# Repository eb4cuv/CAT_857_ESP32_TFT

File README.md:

# CAT_857_ESP32_TFT

This software is based on the well-known ESP32 processor and a 3.5-inch (480x320) TFT touch screen. In its design it has been thought mainly in the simplicity of construction and use as well as in reducing costs.

It is designed to work with the FT857. In other models such as FT817 and FT897 it can work but not all functions are available because the memory map is diferent. It is a pending issue to be developed in the future.

------------------------------------------------------
Este proyecto se ha realizado sobre la base del ya conocido procesador ESP32 https://www.espressif.com/en/products/devkits/esp32-devkitc y un TFT tactil de 3,5 pulgadas (480x320) http://www.lcdwiki.com/3.5inch_SPI_Module_ILI9488_SKU:MSP3520. En su diseño se ha pensado principalmente en la sencillez de construccion y uso asi como en abaratar costes.

Esta diseñado para funcionar con la Yaesu FT857. En otros modelos como la FT817 y FT897 puede funcionar tambien pero no todas las funciones estan disponibles porque la memmoria de unas y otras es disitinta. Es un tema pendiente a desarrollar en un futuro.

------------------------------------------------------

## Estas son algunas de las pantallas:

## Pantalla principal con los VFO's

## Radio de OM y OC

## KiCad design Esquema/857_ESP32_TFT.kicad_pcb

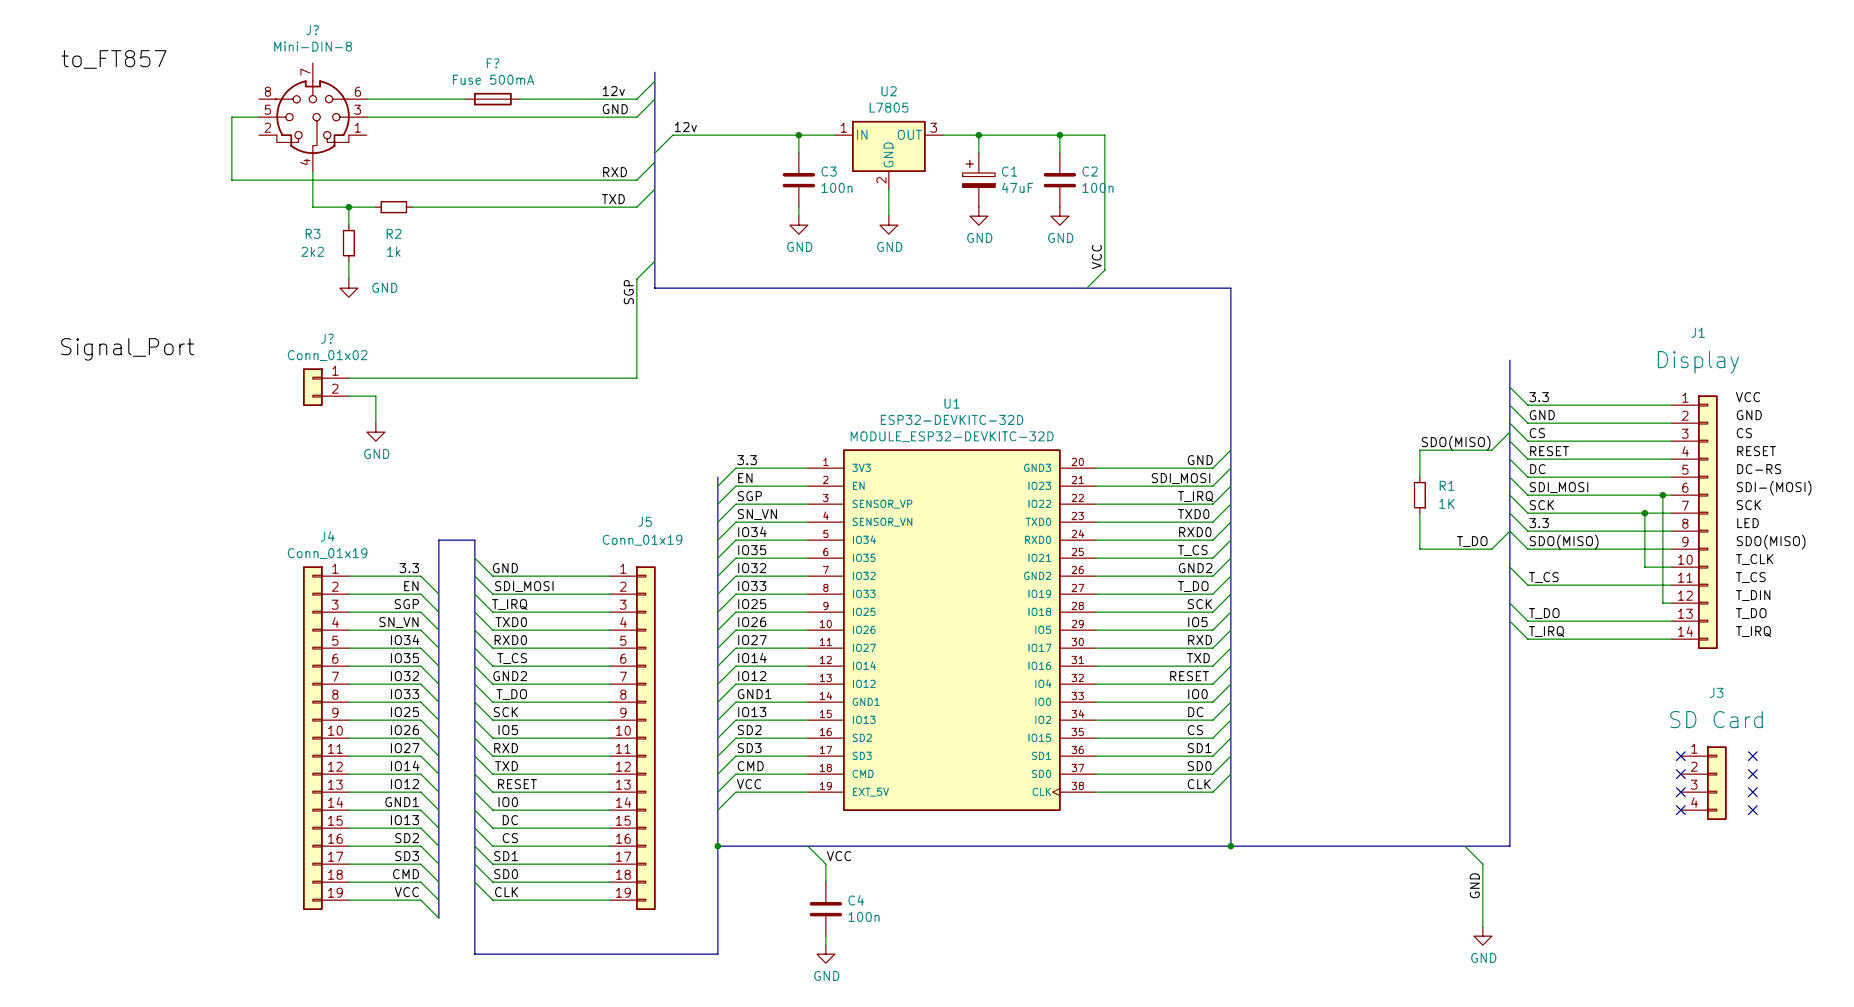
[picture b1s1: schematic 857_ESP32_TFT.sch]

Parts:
C1: 47uF
C2, C3, C4: 100n; C_Rect_L4.6mm_W3.0mm_P2.50mm_MKS02_FKP02
J1: Display; PinHeader_1x14_P2.54mm_Vertical
J3: SD Card; PinHeader_1x04_P2.54mm_Vertical
J4, J5: Conn_01x19; PinHeader_1x19_P2.54mm_Vertical
R1: 1K; R_Axial_DIN0309_L9.0mm_D3.2mm_P12.70mm_Horizontal
R2: 1k; R_Axial_DIN0309_L9.0mm_D3.2mm_P12.70mm_Horizontal
R3: 2k2; R_Axial_DIN0309_L9.0mm_D3.2mm_P12.70mm_Horizontal
U1: ESP32-DEVKITC-32D; MODULE_ESP32-DEVKITC-32D; PARTREV 4
U2: L7805; TO-220-3_Horizontal_TabDown

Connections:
/3.3: J1.1, J1.8, J4.1, U1.1 (3V3)
/12v: C3.1, U2.1 (IN); also elsewhere on the board
/CLK: J5.19, U1.38 (CLK)
/CMD: J4.18, U1.18 (CMD)
/CS: J1.3, J5.16, U1.35 (IO15)
/DC: J1.5, J5.15, U1.34 (IO2)
/EN: J4.2, U1.2 (EN)
/GND1: J4.14, U1.14 (GND1)
/GND2: J5.7, U1.26 (GND2)
/IO0: J5.14, U1.33 (IO0)
/IO5: J5.10, U1.29 (IO5)
/IO12: J4.13, U1.13 (IO12)
/IO13: J4.15, U1.15 (IO13)
/IO14: J4.12, U1.12 (IO14)
/IO25: J4.9, U1.9 (IO25)
/IO26: J4.10, U1.10 (IO26)
/IO27: J4.11, U1.11 (IO27)
/IO32: J4.7, U1.7 (IO32)
/IO33: J4.8, U1.8 (IO33)
/IO34: J4.5, U1.5 (IO34)
/IO35: J4.6, U1.6 (IO35)
/RESET: J1.4, J5.13, U1.32 (IO4)
/RXD: J5.11, U1.30 (IO17); also elsewhere on the board
/RXD0: J5.5, U1.24 (RXD0)
/SCK: J1.7, J1.10, J5.9, U1.28 (IO18)
/SD0: J5.18, U1.37 (SD0)
/SD1: J5.17, U1.36 (SD1)
/SD2: J4.16, U1.16 (SD2)
/SD3: J4.17, U1.17 (SD3)
/SDI_MOSI: J1.6, J1.12, J5.2, U1.21 (IO23)
/SDO(MISO): J1.9, R1.2
/SGP: J4.3, U1.3 (SENSOR_VP); also elsewhere on the board
/SN_VN: J4.4, U1.4 (SENSOR_VN)
/TXD0: J5.4, U1.23 (TXD0)
/T_CS: J1.11, J5.6, U1.25 (IO21)
/T_DO: J1.13, J5.8, R1.1, U1.27 (IO19)
/T_IRQ: J1.14, J5.3, U1.22 (IO22)
/VCC: C1.1, C2.1, C4.1, J4.19, U1.19 (EXT_5V), U2.3 (OUT)
GND: C1.2, C2.2, C3.2, C4.2, J1.2, J5.1, R3.1, U1.20 (GND3), U2.2 (GND); also elsewhere on the board

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
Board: 2 copper layers, 13 parts (0 on the bottom side), 41 nets, no tracks yet.

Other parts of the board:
J2: Conn_01x06; PinHeader_1x06_P2.54mm_Vertical

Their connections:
/12v: J2.1; also elsewhere on the board
/RXD: J2.2; also elsewhere on the board
/SGP: J2.4; also elsewhere on the board
GND: J2.5, J2.6; also elsewhere on the board
